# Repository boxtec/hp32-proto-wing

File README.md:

HelvePic32 Proto Wing Kit

See http://helvepic32.net or http://helvepic32.org/ for more information.

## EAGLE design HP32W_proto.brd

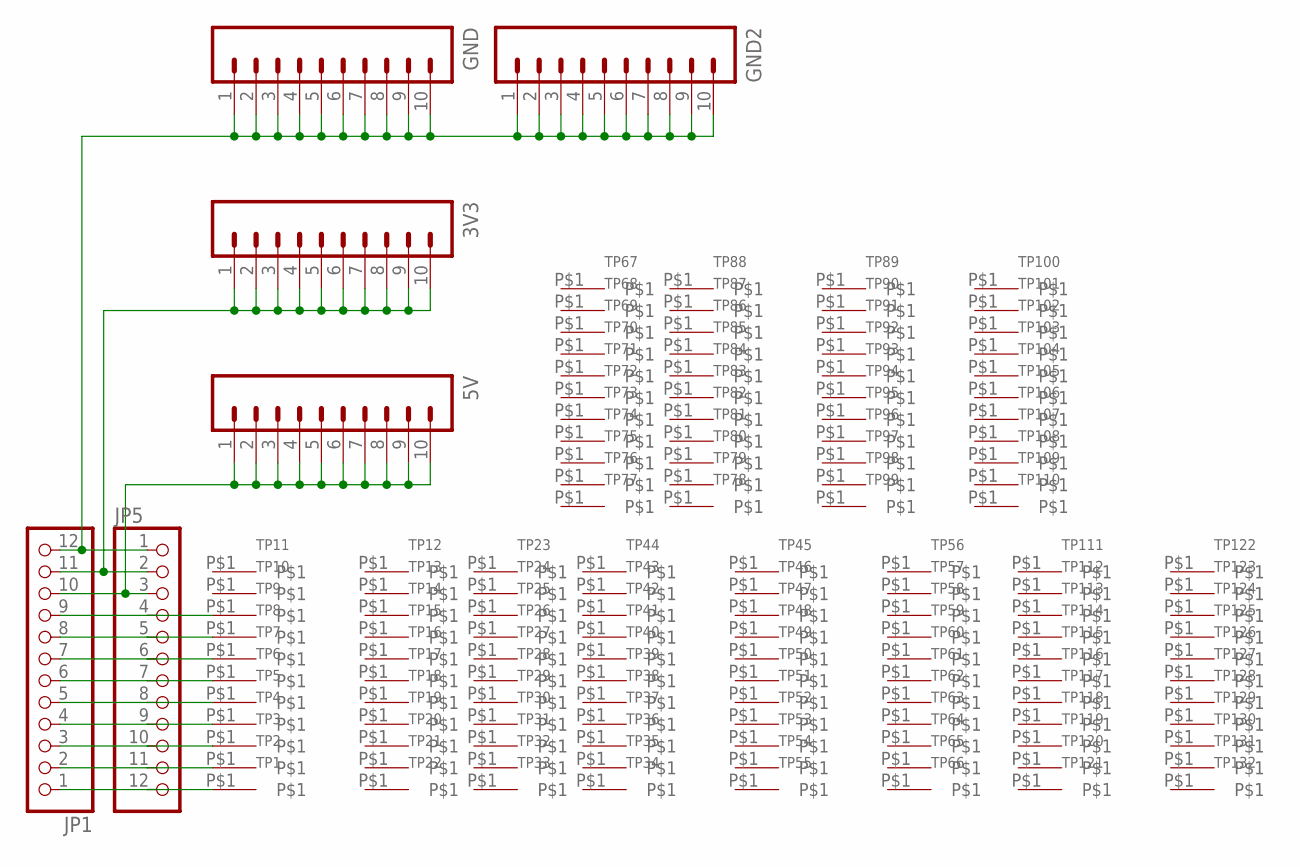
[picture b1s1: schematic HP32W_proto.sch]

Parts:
3V3, 5V: M10"; 1X10
GND, GND2: M10"; 1X10
JP1, JP5: PINHD-1X12-CB; 1X12-CB
TP1, TP2, TP3, TP4, TP5, TP6, TP7, TP8, TP9, TP10, TP11, TP12, TP13, TP14, TP15, TP16, TP17, TP18, TP19, TP20, TP21, TP22, TP23, TP24, TP25, TP26, TP27, TP28, TP29, TP30, TP31, TP32, TP33, TP34, TP35, TP36, TP37, TP38, TP39, TP40, TP41, TP42, TP43, TP44, TP45, TP46, TP47, TP48, TP49, TP50, TP51, TP52, TP53, TP54, TP55, TP56, TP57, TP58, TP59, TP60, TP61, TP62, TP63, TP64, TP65, TP66, TP67, TP68, TP69, TP70, TP71, TP72, TP73, TP74, TP75, TP76, TP77, TP78, TP79, TP80, TP81, TP82, TP83, TP84, TP85, TP86, TP87, TP88, TP89, TP90, TP91, TP92, TP93, TP94, TP95, TP96, TP97, TP98, TP99, TP100, TP101, TP102, TP103, TP104, TP105, TP106, TP107, TP108, TP109, TP110, TP111, TP112, TP113, TP114, TP115, TP116, TP117, TP118, TP119, TP120, TP121, TP122, TP123, TP124, TP125, TP126, TP127, TP128, TP129, TP130, TP131, TP132: FLOWERPIN

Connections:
unnamed: GND.1, GND.2, GND.3, GND.4, GND.5, GND.6, GND.7, GND.8, GND.9, GND.10, GND2.1, GND2.2, GND2.3, GND2.4, GND2.5, GND2.6, GND2.7, GND2.8, GND2.9, GND2.10, JP1.12, JP5.1
unnamed: 3V3.1, 3V3.2, 3V3.3, 3V3.4, 3V3.5, 3V3.6, 3V3.7, 3V3.8, 3V3.9, 3V3.10, JP1.11, JP5.2
unnamed: 5V.1, 5V.2, 5V.3, 5V.4, 5V.5, 5V.6, 5V.7, 5V.8, 5V.9, 5V.10, JP1.10, JP5.3
unnamed: JP1.9, JP5.4, TP9.P$1
unnamed: JP1.8, JP5.5, TP8.P$1
unnamed: JP1.7, JP5.6, TP7.P$1
unnamed: JP1.6, JP5.7, TP6.P$1
unnamed: JP1.5, JP5.8, TP5.P$1
unnamed: JP1.4, JP5.9, TP4.P$1
unnamed: JP1.3, JP5.10, TP3.P$1
unnamed: JP1.2, JP5.11, TP2.P$1
unnamed: JP1.1, JP5.12, TP1.P$1

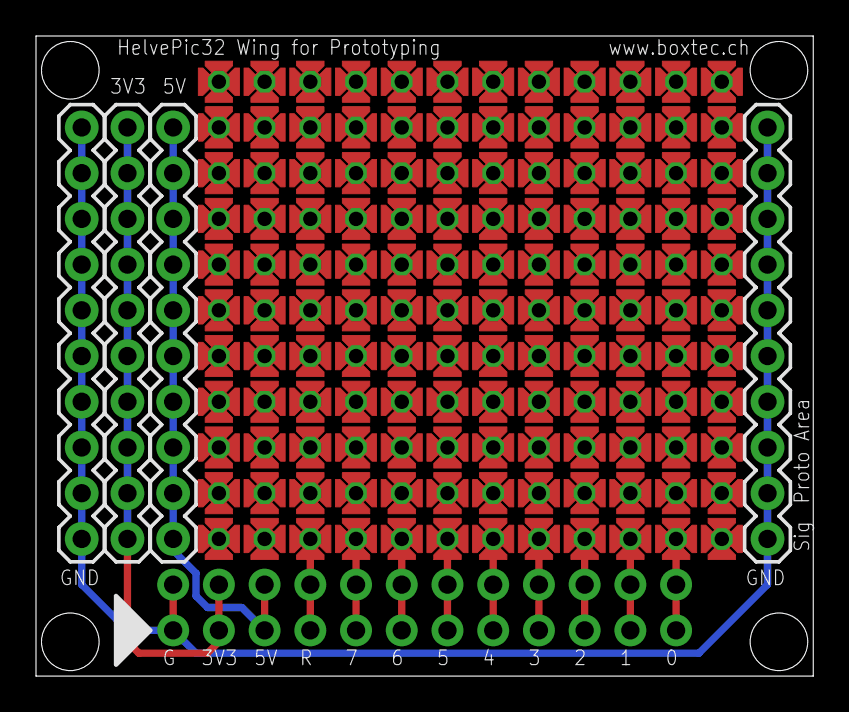
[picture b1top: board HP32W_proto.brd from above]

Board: 2 copper layers, 43.2 x 35.6 mm, 138 parts (0 on the bottom side), 12 nets.

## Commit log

2015-09-30 Initial git import
2015-09-30 link

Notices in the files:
parts and their libraries:
SparkFun-Connectors: Licensing: Creative Commons ShareAlike 4.0 International - https://creativecommons.org/licenses/by-sa/4.0
